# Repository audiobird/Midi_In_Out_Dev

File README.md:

# Midi In / Out Dev board

 Midi dev board that supports 3.3 and 5 volts  
 Selectable via jumper  
 jumpers go from bottom to top of the 2x4 header.  

midi polarity == Type A

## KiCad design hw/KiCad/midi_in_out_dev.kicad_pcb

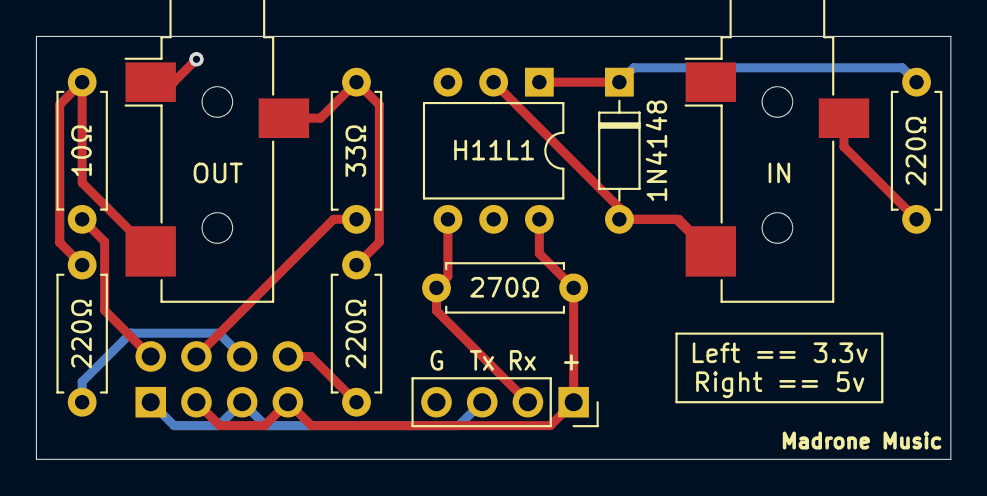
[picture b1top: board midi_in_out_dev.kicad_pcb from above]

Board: 2 copper layers, 50.8 x 23.5 mm, 11 parts (0 on the bottom side), 8 nets.

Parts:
1N4148: 1n4148; D_DO-35_SOD27_P7.62mm_Horizontal
10Ω: 10; R_Axial_DIN0207_L6.3mm_D2.5mm_P7.62mm_Horizontal
33Ω: 33; R_Axial_DIN0207_L6.3mm_D2.5mm_P7.62mm_Horizontal
220Ω, 220Ω#2, 220Ω#3: 220; R_Axial_DIN0207_L6.3mm_D2.5mm_P7.62mm_Horizontal
270Ω: 270; R_Axial_DIN0207_L6.3mm_D2.5mm_P7.62mm_Horizontal
G  TX  RX  +: Conn_01x04_Female; PinSocket_1x04_P2.54mm_Vertical
H11L1: H11L1; DIP-6_W7.62mm
J1: OUT; Jack_3.5mm_CUI_SJ-3523-SMT_Horizontal
J2: IN; Jack_3.5mm_CUI_SJ-3523-SMT_Horizontal

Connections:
+VDC: 270Ω.2, G TX RX +.1, H11L1.6
/UART_RX: 270Ω.1, G TX RX +.2, H11L1.4
GND: G TX RX +.4, H11L1.5, J1.S
unnamed: 1N4148.1, 220Ω#3.1, H11L1.1
unnamed: 1N4148.2, H11L1.2, J2.T
unnamed: 33Ω.1, 220Ω#2.1, J1.R
unnamed: 10Ω.1, 220Ω.1, J1.T
unnamed: 220Ω#3.2, J2.R

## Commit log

2022-02-01 Initial
2022-02-01 stupid link
